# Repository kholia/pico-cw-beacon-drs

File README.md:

#### Details

This project generates a RF signal by toggling a GPIO pin (of a Raspberry Pi
Pico / Pico W board) at a high speed (HF frequency).

Note: The default GPIO pin is `GP2`.

#### Build Steps

Note: This repository has pre-built firmware files in it (`*.uf2` files) for
testing, and debugging purposes.

The following steps demonstrate the process of re-building the firmware from
the source code.

Common steps:

```
sudo apt install cmake gcc-arm-none-eabi libnewlib-arm-none-eabi \
    libstdc++-arm-none-eabi-newlib

sudo apt install gqrx-sdr fldigi pavucontrol pavucontrol-qt pamix
```

```
./build.sh
```

#### Customizations

To customize the CW message, CW speed, and the message, please edit the
`blink.pio` and `message.h` files.

- CW beacon message can be changed in `message.h` file.

- WPM can be changed in `blink.pio` file.

  ```
  // https://www.codebug.org.uk/learn/step/541/morse-code-timing-rules/
  int dit_delay = 92; // 13 WPM
  ```

- RF frequency can be changed in `blink.pio` file.

  The default value targets the 30m band amateur radio band.

Note: Whenever you change these files, please run the following command to
build the firmware file(s).

```
./build_again.sh
```

#### Usage

Write `pio_blink_pico.uf2` to the Raspberry Pi Pico board OR write
`pio_blink_pico_w.uf2` to the Raspberry Pi Pico W board.

To do so, press the BOOTSEL button and hold it while you connect the other end
of the micro USB cable to your computer. This puts your Raspberry Pi Pico into
USB mass storage device mode. Drag and drop the appropriate .uf2 file to the
`Pico` drive.

Attach picocom or another serial terminal program to `/dev/ttyACM0` (typically)
for added fun.

https://projects.raspberrypi.org/en/projects/getting-started-with-the-pico has
additional details on this process.

Monitor the lower 30m or 144 MHz (2m) band using a SDR for receiving the CW
beacon.

#### Amplifier Options

- [QRPp-Amplifier-v2](./QRPp-Amplifier-v2)
- [QRPp-Amplifier-v3](./QRPp-Amplifier-v3)
- https://antrak.org.tr/blog/adx-arduino-digital-transceiver/ - ADX PA

#### Future Ideas

- Implement FM modulation for the `VHF Fox`.

#### PCB Render

[UPDATE] The first version of the PCB was successfully validated on
26th-October-2022.

Output is > 3.25W (~36.2Vpp) @ 14 MHz @ 13v with the ADX LPF filter.

Use `27 SWG winding wire` in the ADX LPF filter.

#### Automatic CW Decoding

Setup a virtual audio cable:

```
pacmd load-module module-null-sink sink_name=Virtual0
pacmd update-sink-proplist Virtual0 device.description=Virtual0
pacmd update-source-proplist Virtual0.monitor device.description=Virtual0
```

Ask Gqrx to output audio to this `Virtual0` device.

Use `PulseAudio` device in Fldigi.

Using `pavucontrol` redirect the Fldigi input to come from `Virtual0`. Go to
the `Recording` tab in `pavucontrol` to do this.

You are all set for automatic CW decoding using `Fldigi` software now. Set `Op
Mode` to `CW` in Fldigi.

...

On Android, you can use the `Morse Expert` app for automatic CW decoding.

#### Credits

- Bradshaw Lupton - K1TE

- Gajendra Kumar - VU2BGS

- Barb - WB2CBA

#### References

- https://github.com/raspberrypi/pico-examples/blob/master/picoboard/blinky/blinky.c
- https://antrak.org.tr/blog/adx-arduino-digital-transceiver/
- https://github.com/WB2CBA/ADX

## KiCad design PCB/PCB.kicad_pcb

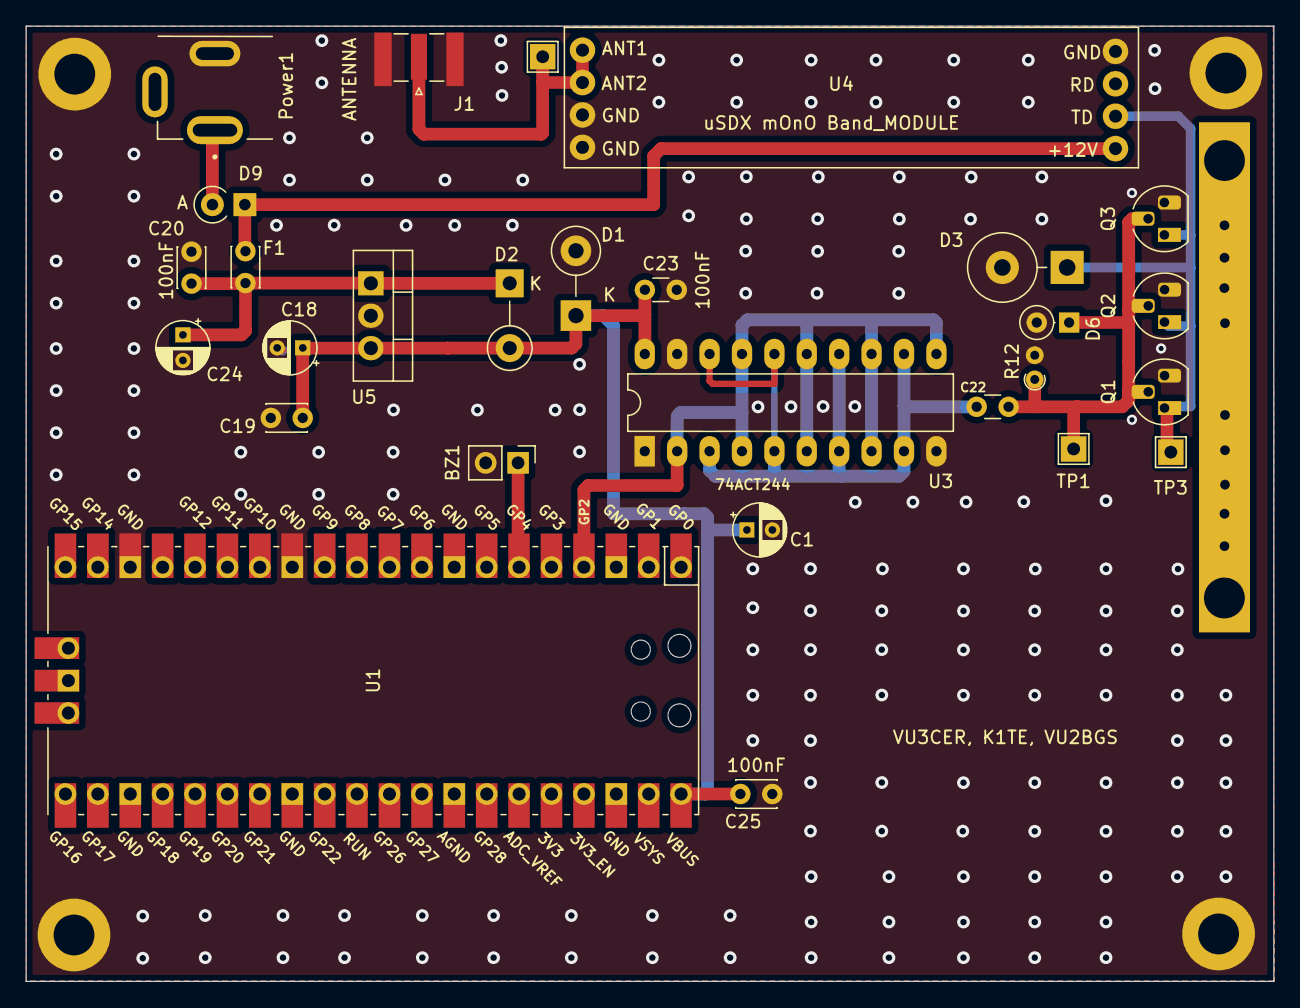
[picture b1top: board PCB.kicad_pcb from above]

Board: 2 copper layers, 97.8 x 74.9 mm, 33 parts (0 on the bottom side), 11 nets.

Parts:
BZ1: Buzzer; PinHeader_1x02_P2.54mm_Vertical
C1: 10uF; CP_Radial_D4.0mm_P2.00mm
C18: 10uF/16V; CP_Radial_D4.0mm_P2.00mm
C19, C20, C25: 100nF; C_Disc_D3.0mm_W2.0mm_P2.50mm
C22, C23: 100nF; C_Disc_D3.0mm_W1.6mm_P2.50mm
C24: 100uF/16V; CP_Radial_D4.0mm_P2.00mm
D1: 5.6V 5W; D_DO-15_P5.08mm_Vertical_KathodeUp
D2: 1N4001; D_DO-41_SOD81_P5.08mm_Vertical_KathodeUp
D3: 47v 5W; D_DO-201_P5.08mm_Vertical_KathodeUp
D6: 1N4148; D_DO-35_SOD27_P2.54mm_Vertical_KathodeUp
D9: 1N5817; D_A-405_P2.54mm_Vertical_KathodeUp
F1: 1A; C_Disc_D3.0mm_W2.0mm_P2.50mm
H1, H2, H3, H4: MountingHole_Pad; MountingHole_3.2mm_M3_ISO7380_Pad
HS1: Heatsink_Pad; ThermalPad_Final
J1: SMA; SMA_Samtec_SMA-J-P-X-ST-EM1_EdgeMount
Power1: DC-005 (Barrel Jack); XKB_DC-005-5A-2.0_Modded
Q1, Q2, Q3: BS170; TO-92_HandSolder
R12: 2.7k; R_Axial_DIN0204_L3.6mm_D1.6mm_P1.90mm_Vertical
TP1, TP3, TP4: TestPoint; TestPoint_THTPad_2.0x2.0mm_Drill1.0mm
U1: Pico; RPi_Pico_SMD_TH
U3: 74ACT244; DIP-20_W7.62mm_LongPads
U4: uSDX mOnO Band_MODULE; uSDX_LPF_Band_Module
U5: CDIL_7805_TO220; TO-220-3_Vertical

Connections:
+5V: C1.1, C18.1, C19.1, C23.1, C25.2, D1.1 (K), D2.2 (A), U1.40 (VBUS), U3.20 (VCC), U5.3 (VO)
GND: BZ1.2 (+), C1.2, C18.2, C19.2, C20.2, C23.2, C24.2, C25.1, D1.2 (A), D3.2 (A), D6.2 (A), H1.1, H2.1, H3.1, H4.1, J1.2 (Ext), Power1.2, Q1.3 (S), Q2.3 (S), Q3.3 (S), R12.2, U1.13 (GND), U1.18 (GND), U3.1 (OEa), U3.10 (GND), U3.19 (OEb), U4.4 (GND), U4.7 (GND), U4.8 (GND), U5.2 (GND)
unnamed: BZ1.1 (-), U1.6 (GPIO4)
unnamed: C20.1, C24.1, D2.1 (K), F1.2, U5.1 (VI)
unnamed: C22.1, D6.1 (K), Q1.2 (G), Q2.2 (G), Q3.2 (G), R12.1, TP1.1
unnamed: C22.2, U3.3 (O3b), U3.5 (O2b), U3.7 (O1b), U3.9 (O0b), U3.12 (O3a), U3.14 (O2a), U3.16 (O1a), U3.18 (O0a)
unnamed: D9.1 (K), F1.1, U4.1 (+12V)
unnamed: D9.2 (A), Power1.1
unnamed: J1.1 (In), TP4.1, U4.5 (ANT1), U4.6 (ANT2)
unnamed: U1.4 (GPIO2), U3.2 (I0a), U3.4 (I1a), U3.6 (I2a), U3.8 (I3a), U3.11 (I0b), U3.13 (I1b), U3.15 (I2b), U3.17 (I3b)
TD_IN: D3.1 (K), Q1.1 (D), Q2.1 (D), Q3.1 (D), TP3.1, U4.2 (TD)

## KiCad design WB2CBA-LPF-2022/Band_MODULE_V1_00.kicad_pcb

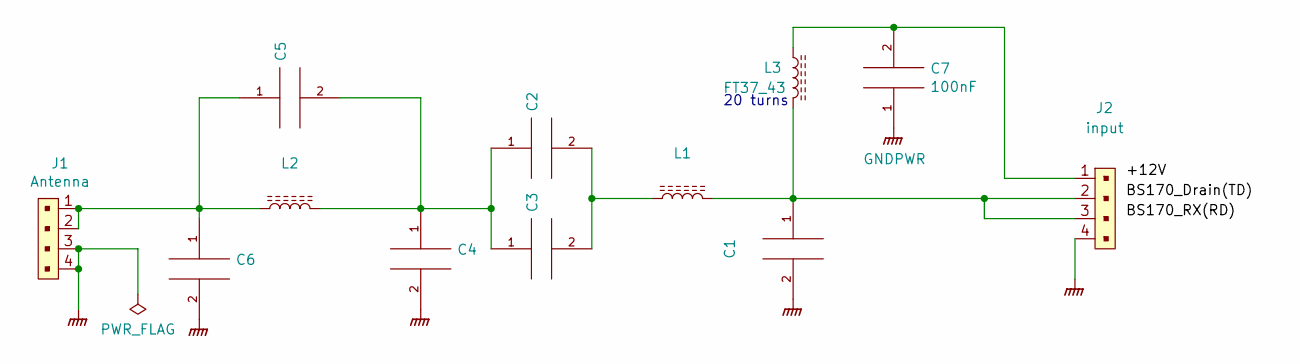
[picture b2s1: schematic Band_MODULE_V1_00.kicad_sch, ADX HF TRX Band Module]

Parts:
C1, C2, C3, C4, C5, C6: C_Disc_D5.0mm_W2.5mm_P2.50mm
C7: 100nF; C_Disc_D5.0mm_W2.5mm_P2.50mm
J1: Antenna; PinHeader_1x4_P2.54mm_Drill1.02mm; MPN 0022232041; Digi-Key_PN WM4202-ND
J2: input; PinHeader_1x4_P2.54mm_Drill1.02mm; MPN 0022232041; Digi-Key_PN WM4202-ND
L1, L2: L_Toroid_Vertical_L10.0mm_W5.0mm_P5.08mm
L3: FT37_43; L_Toroid_Vertical_L10.0mm_W5.0mm_P5.08mm

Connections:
GNDPWR: C1.2, C4.2, C6.2, C7.1, J1.3, J1.4, J2.4
unnamed: C1.1, J2.2, J2.3, L1.2, L3.2
unnamed: C2.1, C3.1, C4.1, C5.2, L2.2
unnamed: C2.2, C3.2, L1.1
unnamed: C5.1, C6.1, J1.1, J1.2, L2.1
unnamed: C7.2, J2.1, L3.1

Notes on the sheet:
20 turns

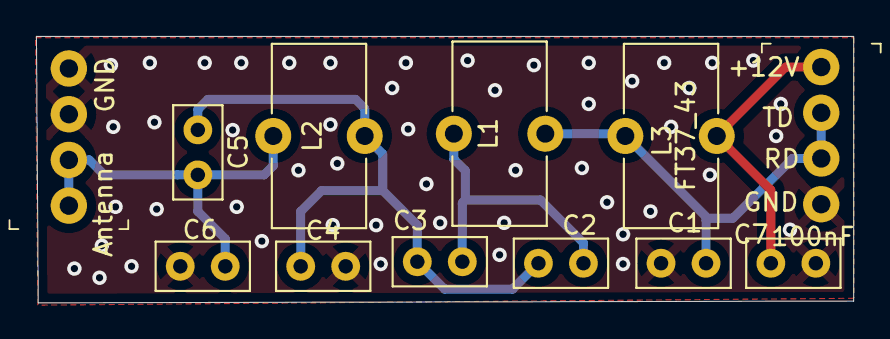
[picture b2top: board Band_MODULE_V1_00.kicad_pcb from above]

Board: 2 copper layers, 45.4 x 14.8 mm, 12 parts (0 on the bottom side), 6 nets.

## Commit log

2022-10-26 Make HF CW Beacon on 30m band the default
2022-10-26 Backups + Changes
2022-10-26 Make 20m the default for testing
2023-11-30 PCB v2 - minor tweaks
